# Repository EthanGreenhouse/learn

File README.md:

# 📚 learn

Collection of hardware and software mini projects documenting my learning journey.

- [AutoCAD](https://github.com/EthanGreenhouse/learn/tree/main/autocad)
- [C++](https://github.com/EthanGreenhouse/learn/tree/main/cpp)
- [KiCad](https://github.com/EthanGreenhouse/learn/tree/2df7803e8e1d99afe89c78c807994d671dcfed1c/kicad)
- [MATLAB](https://github.com/EthanGreenhouse/learn/tree/main/matlab)
- [Python](https://github.com/EthanGreenhouse/learn/tree/main/python)
- [Solidworks](https://github.com/EthanGreenhouse/learn/tree/main/solidworks)

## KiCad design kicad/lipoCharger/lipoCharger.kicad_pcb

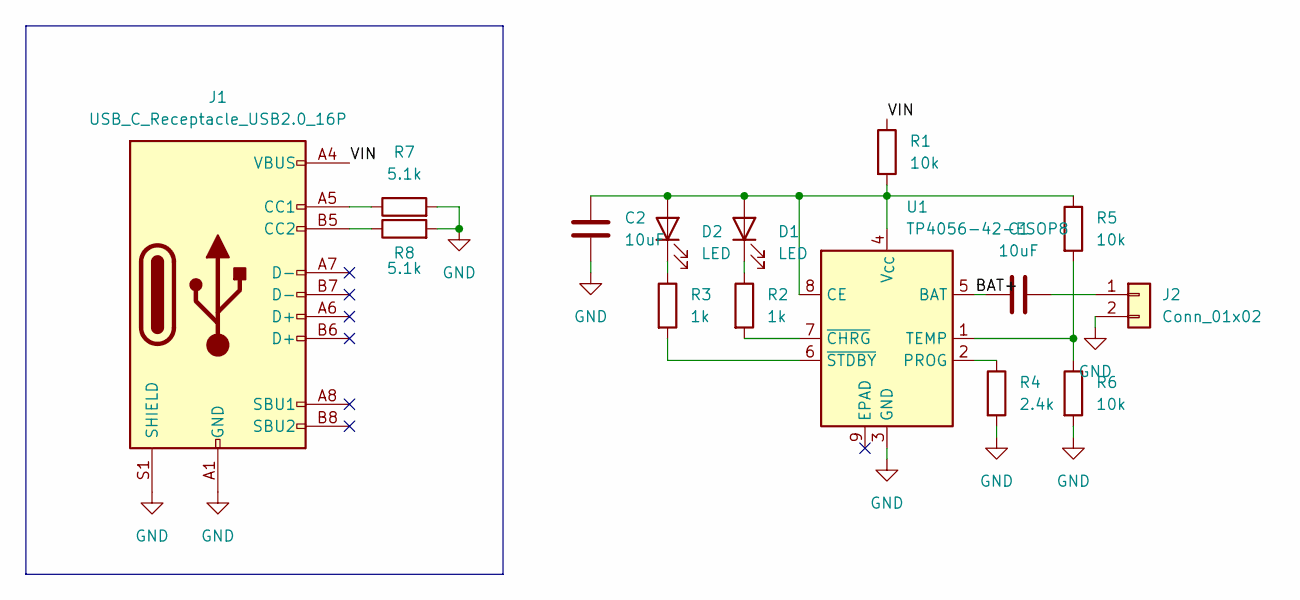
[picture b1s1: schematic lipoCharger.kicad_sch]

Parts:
C1, C2: 10uF; C_0805_2012Metric
D1, D2: LED; LED_0805_2012Metric
J1: USB_C_Receptacle_USB2.0_16P; USB_C_Receptacle_G-Switch_GT-USB-7010ASV
J2: Conn_01x02; JST_PH_B2B-PH-K_1x02_P2.00mm_Vertical
R1, R5, R6: 10k; R_0805_2012Metric
R2, R3: 1k; R_0805_2012Metric
R4: 2.4k; R_0805_2012Metric
R7, R8: 5.1k; R_0805_2012Metric
U1: TP4056-42-ESOP8; SOIC-8-1EP_3.9x4.9mm_P1.27mm_EP2.41x3.3mm_ThermalVias

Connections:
/BAT+: C1.1, U1.5 (BAT)
/VIN: J1.A4 (VBUS), J1.A9 (VBUS), J1.B4 (VBUS), J1.B9 (VBUS), R1.1
GND: C2.1, J1.A1 (GND), J1.A12 (GND), J1.B1 (GND), J1.B12 (GND), J1.S1 (SHIELD), J2.2, R4.2, R6.2, R7.2, R8.2, U1.3 (GND)
unnamed: C2.2, D1.2 (A), D2.2 (A), R1.2, R5.1, U1.4 (V_{CC}), U1.8 (CE)
unnamed: D1.1 (K), R2.1
unnamed: D2.1 (K), R3.1
unnamed: J1.A5 (CC1), R7.1
unnamed: J1.B5 (CC2), R8.1
unnamed: C1.2, J2.1
unnamed: R4.1, U1.2 (PROG)
unnamed: R5.2, R6.1, U1.1 (TEMP)
unnamed: R2.2, U1.7 (~CHRG)
unnamed: R3.2, U1.6 (~STDBY)

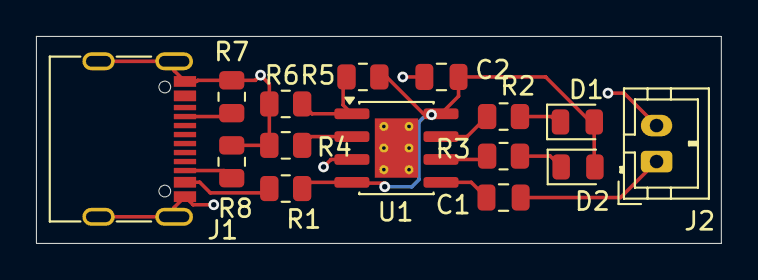
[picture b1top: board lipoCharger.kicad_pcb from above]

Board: 2 copper layers, 38.0 x 11.5 mm, 15 parts (0 on the bottom side), 13 nets.

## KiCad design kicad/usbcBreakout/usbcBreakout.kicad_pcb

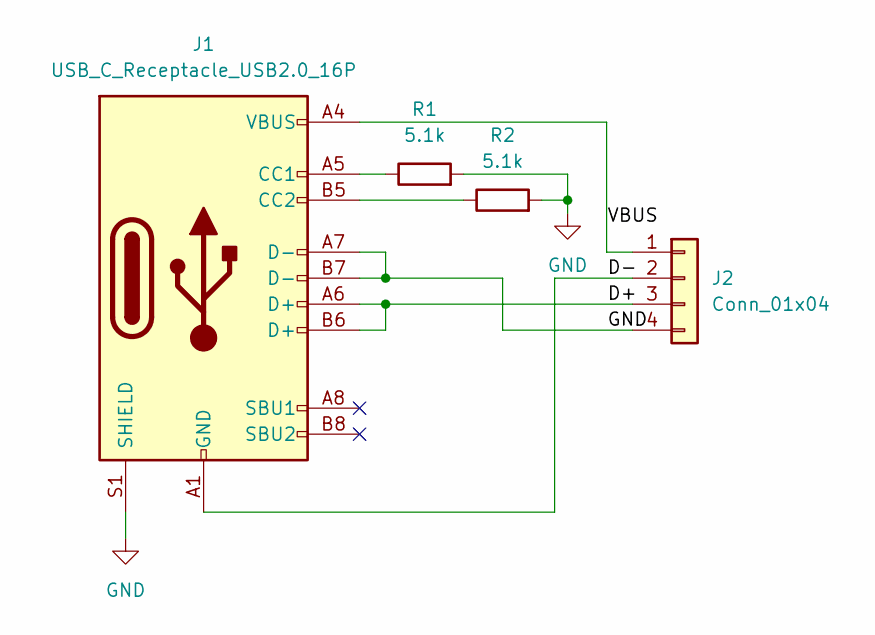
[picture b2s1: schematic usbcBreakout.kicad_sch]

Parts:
J1: USB_C_Receptacle_USB2.0_16P; USB_C_Receptacle_G-Switch_GT-USB-7010ASV
J2: Conn_01x04; PinHeader_1x04_P2.54mm_Vertical
R1, R2: 5.1k; R_0805_2012Metric

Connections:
/D+: J1.A6 (D+), J1.B6 (D+), J2.3
/D-: J1.A1 (GND), J1.A12 (GND), J1.B1 (GND), J1.B12 (GND), J2.2
/VBUS: J1.A4 (VBUS), J1.A9 (VBUS), J1.B4 (VBUS), J1.B9 (VBUS), J2.1
GND: J1.A7 (D-), J1.B7 (D-), J1.S1 (SHIELD), J2.4, R1.2, R2.2
unnamed: J1.A5 (CC1), R1.1
unnamed: J1.B5 (CC2), R2.1

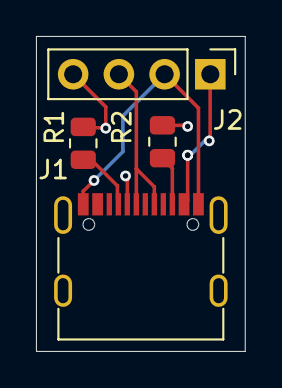
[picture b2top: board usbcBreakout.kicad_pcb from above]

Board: 2 copper layers, 11.6 x 17.5 mm, 4 parts (0 on the bottom side), 6 nets.

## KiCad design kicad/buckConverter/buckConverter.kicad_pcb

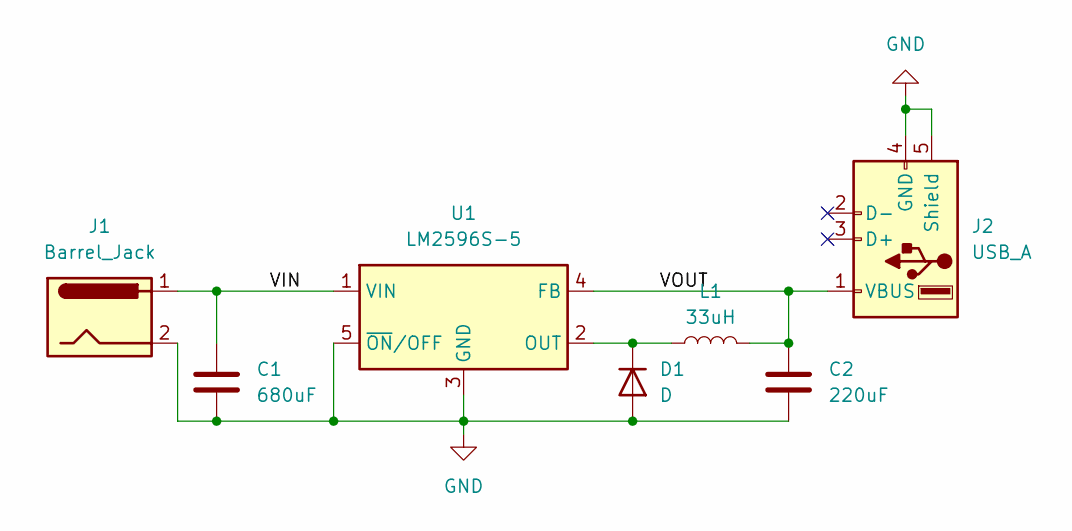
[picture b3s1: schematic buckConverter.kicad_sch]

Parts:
C1: 680uF; CP_Radial_D10.0mm_P5.00mm
C2: 220uF; CP_Radial_D10.0mm_P5.00mm
D1: D; D_0805_2012Metric
J1: Barrel_Jack; BarrelJack_Horizontal
J2: USB_A; USB_A_Molex_48037-2200_Horizontal
L1: 33uH; L_Radial_D12.0mm_P6.00mm_Murata_1900R
U1: LM2596S-5; TO-263-5_TabPin3

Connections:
/VIN: C1.2, J1.1, U1.1 (VIN)
/VOUT: C2.2, J2.1 (VBUS), L1.2, U1.4 (FB)
GND: C1.1, C2.1, D1.2 (A), J1.2, J2.4 (GND), J2.5 (Shield), U1.3 (GND), U1.5 (~ON/OFF)
unnamed: D1.1 (K), L1.1, U1.2 (OUT)

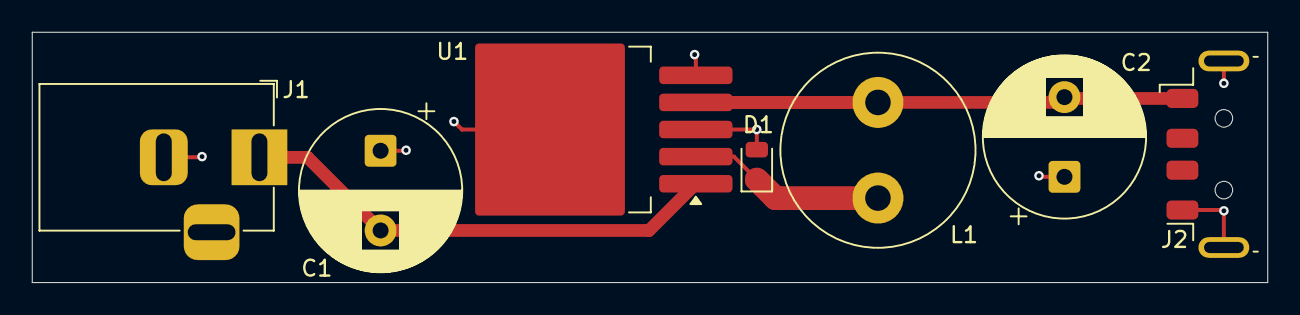
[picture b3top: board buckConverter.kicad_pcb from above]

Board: 2 copper layers, 77.5 x 15.7 mm, 7 parts (0 on the bottom side), 4 nets.

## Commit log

2025-10-24 Revise README with new title and project details
    Updated repository title and expanded project description.
2025-10-24 Add links to hardware and software projects
2025-12-15 Edit README
    Removed the Hardware design section from the README.
2026-02-23 Refactor bit manipulation program structure
2026-02-23 Implement integer format display and calculations
2026-02-23 Rename
